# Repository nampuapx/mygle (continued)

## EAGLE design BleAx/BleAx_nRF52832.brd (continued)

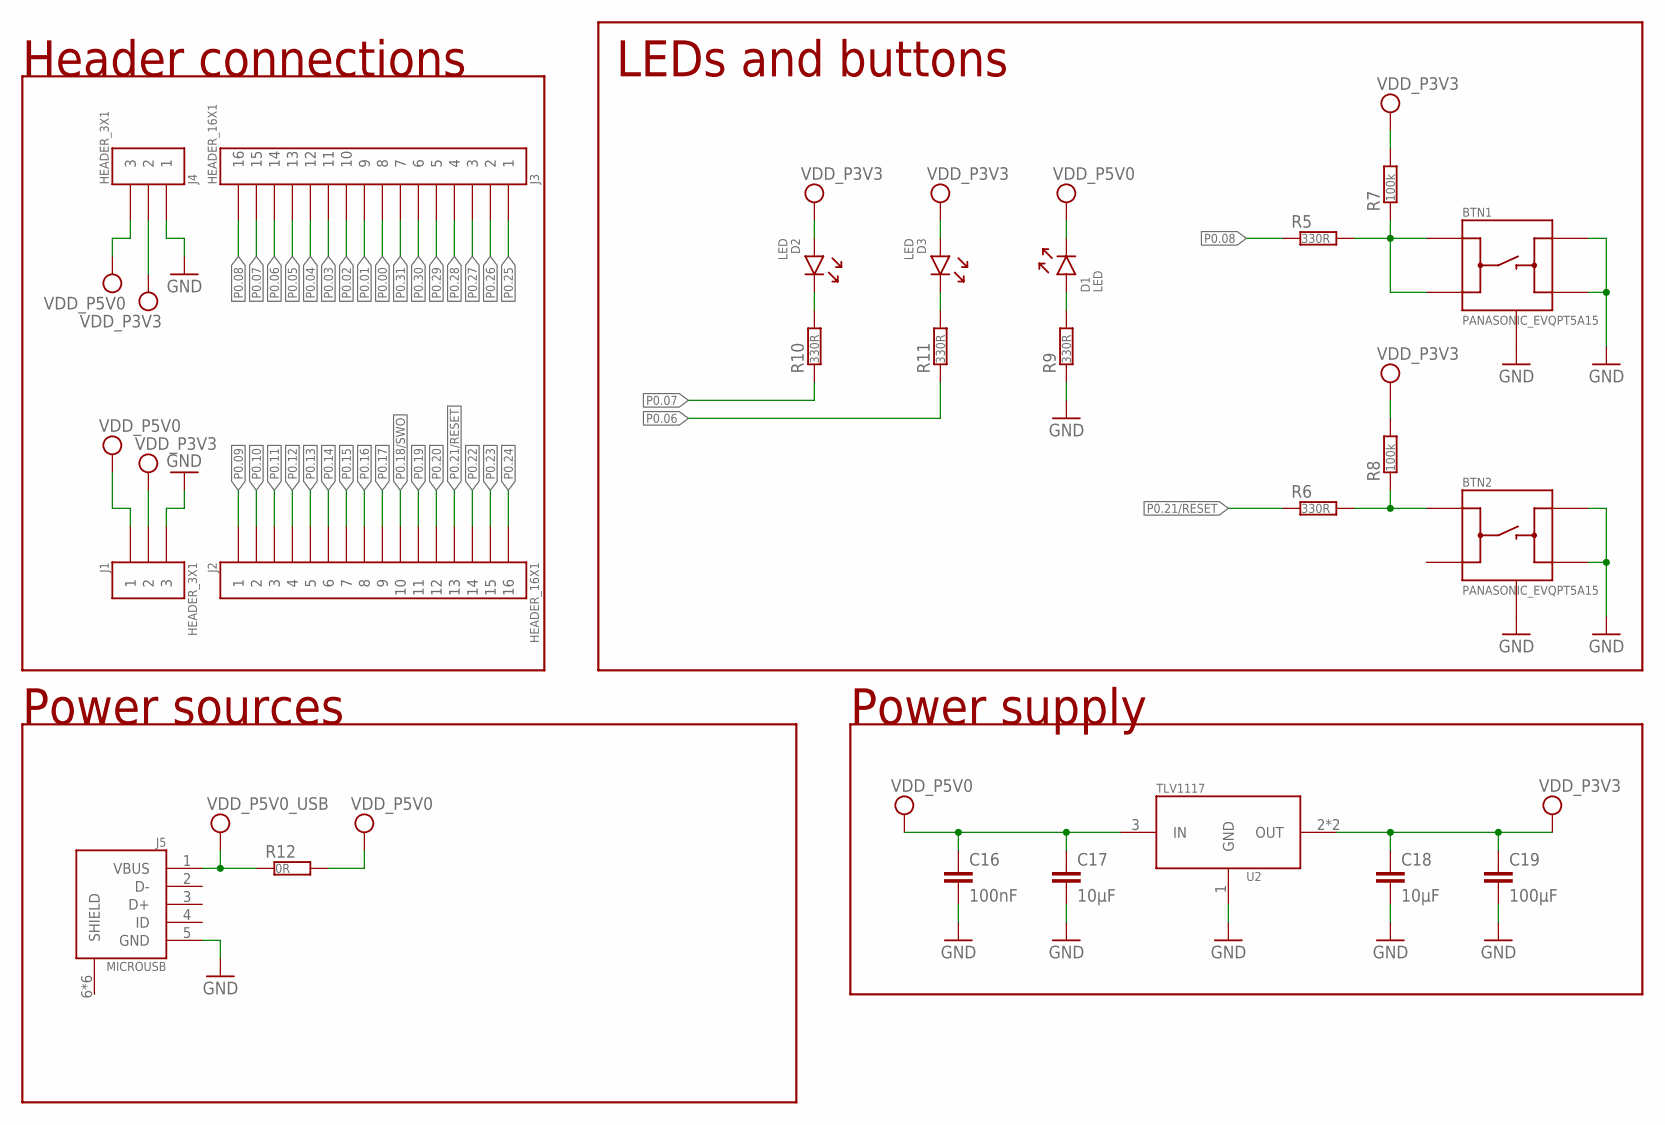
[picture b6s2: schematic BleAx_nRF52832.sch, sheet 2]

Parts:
BTN1, BTN2: PANASONIC_EVQPT5A15
C16: 100nF; RESC0402_N
C17, C18: 10µF; RESC0603_N
C19: 100µF; RESC0805_N
D1, D2, D3: LED; DIOC0603_N
J1, J4: HEADER_3X1; HDRV3W64P254_1X3_762X254X900B_NO_SILK
J2, J3: HEADER_16X1; HDRV16W64P254_1X16_4064X254X900B_NO_SILK
J5: MICROUSB; USB-MICRO-B-RA-SMD-PIP
R5, R6, R9, R10, R11: 330R; RESC0402_N
R7, R8: 100k; RESC0402_N
R12: 0R; RESC0402_N
U2: TLV1117; SOT220P700-4_N

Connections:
GND: BTN1.3 (B), BTN1.4 (B'), BTN1.5 (GND), BTN1.6 (GND), BTN2.3 (B), BTN2.4 (B'), BTN2.5 (GND), BTN2.6 (GND), C16.2, C17.2, C18.2, C19.2, J1.P$3 (3), J4.P$1 (1), J5.5 (GND), R9.1, U2.1 (GND); also elsewhere on the board
unnamed: BTN2.1 (A), R6.2, R8.1
unnamed: BTN1.1 (A), BTN1.2 (A'), R5.2, R7.1
unnamed: D2.1 (C), R10.2
unnamed: D3.1 (C), R11.2
P0.00: J3.P$8 (8)
P0.01: J3.P$9 (9)
P0.02: J3.P$10 (10); also elsewhere on the board
P0.03: J3.P$11 (11); also elsewhere on the board
P0.04: J3.P$12 (12); also elsewhere on the board
P0.05: J3.P$13 (13); also elsewhere on the board
P0.06: J3.P$14 (14), R11.1; also elsewhere on the board
P0.07: J3.P$15 (15), R10.1; also elsewhere on the board
P0.08: J3.P$16 (16), R5.1; also elsewhere on the board
P0.09: J2.P$1 (1); also elsewhere on the board
P0.10: J2.P$2 (2); also elsewhere on the board
P0.11: J2.P$3 (3); also elsewhere on the board
P0.12: J2.P$4 (4); also elsewhere on the board
P0.13: J2.P$5 (5); also elsewhere on the board
P0.14: J2.P$6 (6); also elsewhere on the board
P0.15: J2.P$7 (7); also elsewhere on the board
P0.16: J2.P$8 (8); also elsewhere on the board
P0.17: J2.P$9 (9); also elsewhere on the board
P0.18/SWO: J2.P$10 (10); also elsewhere on the board
P0.19: J2.P$11 (11); also elsewhere on the board
P0.20: J2.P$12 (12); also elsewhere on the board
P0.21/RESET: J2.P$13 (13), R6.1; also elsewhere on the board
P0.22: J2.P$14 (14); also elsewhere on the board
P0.23: J2.P$15 (15); also elsewhere on the board
P0.24: J2.P$16 (16); also elsewhere on the board
P0.25: J3.P$1 (1); also elsewhere on the board
P0.26: J3.P$2 (2); also elsewhere on the board
P0.27: J3.P$3 (3); also elsewhere on the board
P0.28: J3.P$4 (4); also elsewhere on the board
P0.29: J3.P$5 (5); also elsewhere on the board
P0.30: J3.P$6 (6); also elsewhere on the board
P0.31: J3.P$7 (7); also elsewhere on the board
VCC_P5V0_USB: J5.1 (VBUS), R12.1
VDD_LED: D1.2 (A), R9.2
VDD_P3V3: C18.1, C19.1, D2.2 (A), D3.2 (A), J1.P$2 (2), J4.P$2 (2), R7.2, R8.2, U2.2 (OUT), U2.4 (OUT); also elsewhere on the board
VDD_P5V0: C16.1, C17.1, D1.1 (C), J1.P$1 (1), J4.P$3 (3), R12.2, U2.3 (IN)

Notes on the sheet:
Power supply
Power sources
Header connections
LEDs and buttons

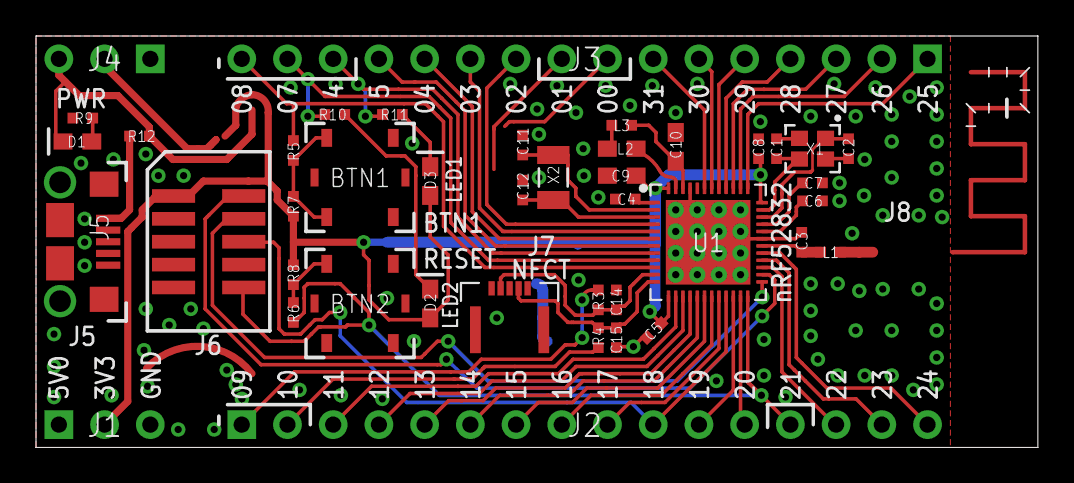
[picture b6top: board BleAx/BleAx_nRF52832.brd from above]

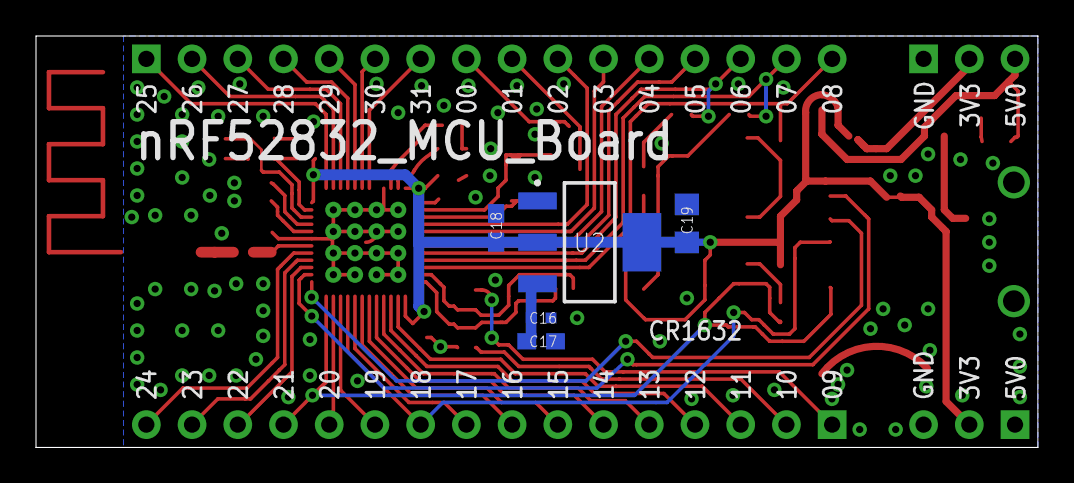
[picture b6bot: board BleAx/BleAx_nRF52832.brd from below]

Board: 2 copper layers, 55.7 x 22.9 mm, 48 parts (5 on the bottom side), 55 nets.

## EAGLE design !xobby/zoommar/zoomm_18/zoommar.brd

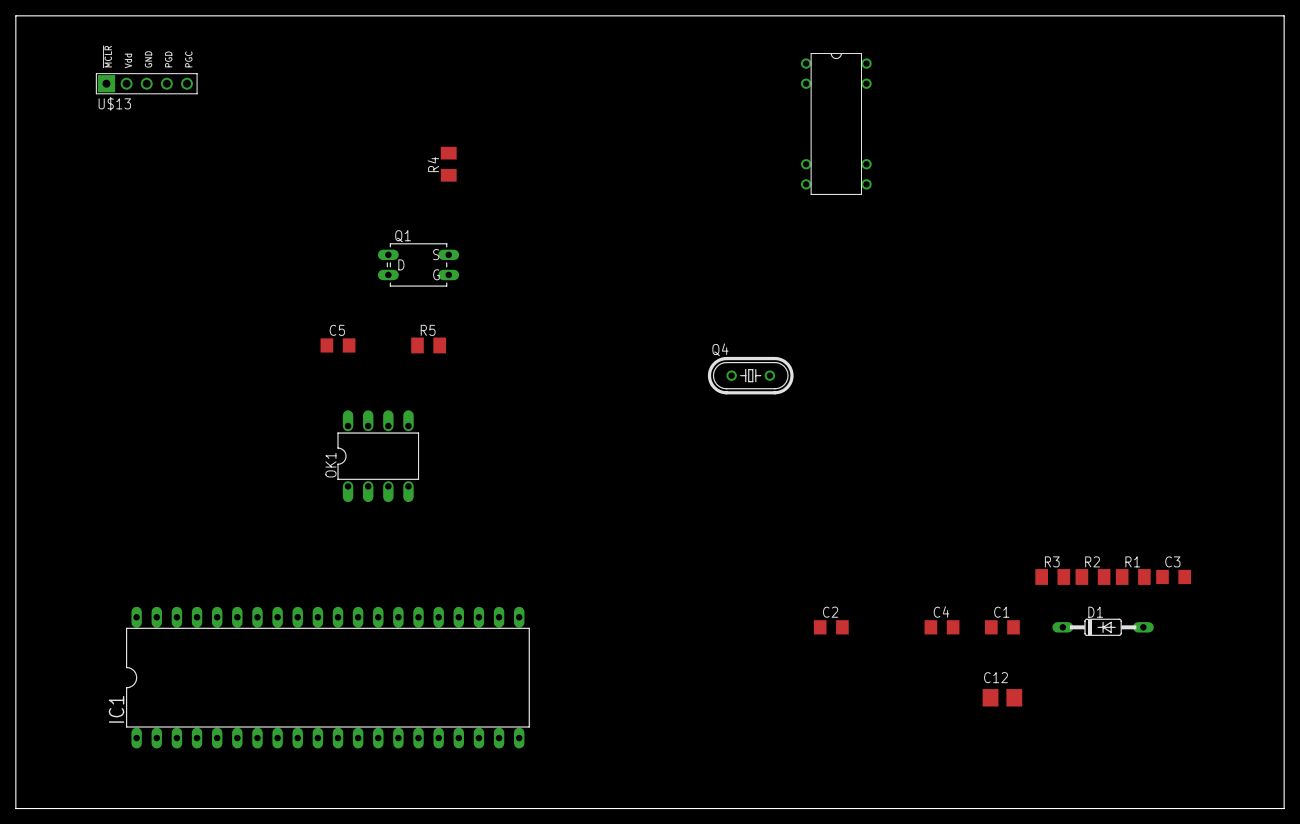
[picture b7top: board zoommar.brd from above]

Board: 2 copper layers, 160.0 x 100.0 mm, 18 parts (0 on the bottom side), 13 nets, no tracks yet.

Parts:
C1, C4, C5: 0.47uF; C1206
C2, C3: 15pF; C1206
C12: 10u; CT3528
D1: 1N4148DO35-10; DO35-10
IC1: PIC18F4550_40; DIL40
OK1: 6N138; DIL08
Q1: IRFD9120; C370-01
Q4: 20MHz; HC49/S
R1: 10k; M1206
R2: 3k3; M1206
R3: 220; M1206
R4: 10e; M1206
R5: 5k; M1206
U$1: TRR2A05D00; TRR_DIP
U$13: PIC-PROG-CON

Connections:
+5V: C1.2, C4.2, C12.-, IC1.11, IC1.32, OK1.8, R1.2, R2.2, R4.2, U$1.1
GND: C1.1, C2.2, C3.1, C4.1, C5.1, C12.+, IC1.12, IC1.31, OK1.5, Q1.D1, U$1.6, U$13.3
MCLR: IC1.1, R1.1, U$13.1
unnamed: IC1.40, U$13.4
unnamed: IC1.39, U$13.5
unnamed: Q1.S, R4.1, U$1.2
unnamed: D1.C, OK1.2, R3.1
unnamed: D1.A, OK1.3
unnamed: C5.2, Q1.G, R5.1
unnamed: R5.2, U$1.7
OSC@1: C2.1, Q4.1
OSC@2: C3.2, Q4.2
RX: IC1.26, OK1.6, R2.1

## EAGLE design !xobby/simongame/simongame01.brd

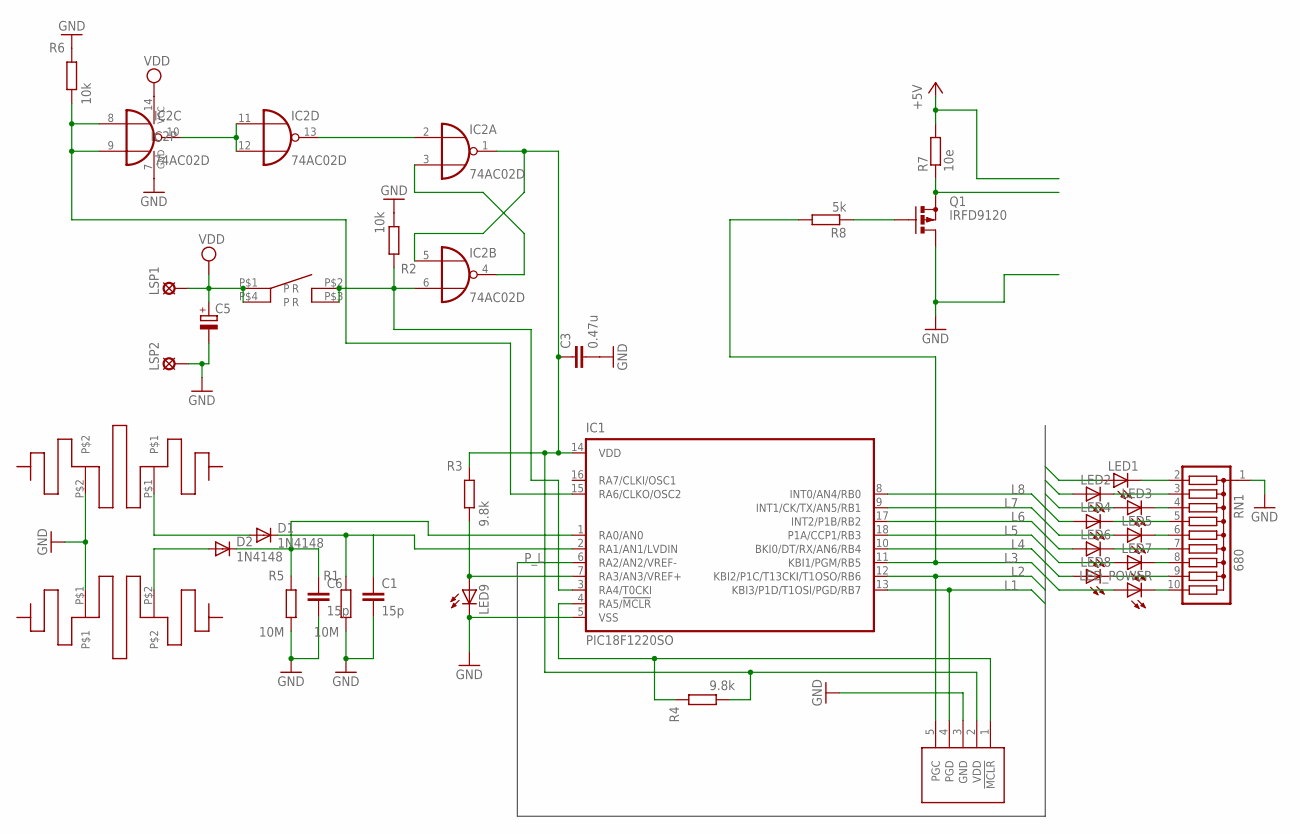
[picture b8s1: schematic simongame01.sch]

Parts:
C1, C6: 15p; C1206
C3: 0.47u; C1206
C5: CPOL-EUSMCA; SMC_A
D1, D2: 1N4148; DO35-10
IC1: PIC18F1220SO; SO-18W
IC2: 74AC02D; SO14
LED1, LED2, LED3, LED4, LED5, LED6, LED7, LED8: LED3MM
LED9: LED5MM
LED_POWER: LED3MM
LSP1, LSP2: SE14
Q1: IRFD9120; C370-01
R1, R5: 10M; M1206
R2, R6: 10k; M1206
R3, R4: 9.8k; M1206
R7: 10e; M1206
R8: 5k; M1206
RN1: 680; SIL10
U$1: TIKBUTTON01
U$2, U$3: ANTENNA; ANT!
U$4: PIC-PROG-CON

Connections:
+5V: R7.2
GND: C1.2, C3.2, C5.-, C6.2, IC1.5 (VSS), IC2.7 (GND), LED9.K (C), LSP2.MP, Q1.D1, R1.1, R2.1, R5.1, R6.2, RN1.1, U$2.P$1, U$3.P$2, U$4.3 (GND)
L1: IC1.13 (KBI3/P1D/T1OSI/PGD/RB7), LED1.A, U$4.4 (PGD)
L2: IC1.12 (KBI2/P1C/T13CKI/T1OSO/RB6), LED2.A, U$4.5 (PGC)
L3: IC1.11 (KBI1/PGM/RB5), LED3.A, R8.2
L4: IC1.10 (BKI0/DT/RX/AN6/RB4), LED4.A
L5: IC1.18 (P1A/CCP1/RB3), LED5.A
L6: IC1.17 (INT2/P1B/RB2), LED6.A
L7: IC1.9 (INT1/CK/TX/AN5/RB1), LED7.A
L8: IC1.8 (INT0/AN4/RB0), LED8.A
unnamed: C1.1, D1.C, IC1.2 (RA1/AN1/LVDIN), R1.2
unnamed: C6.1, D2.C, IC1.1 (RA0/AN0), R5.2
unnamed: LED1.K (C), RN1.2
unnamed: LED2.K (C), RN1.3
unnamed: LED3.K (C), RN1.4
unnamed: LED4.K (C), RN1.5
unnamed: LED5.K (C), RN1.6
unnamed: LED6.K (C), RN1.7
unnamed: LED7.K (C), RN1.8
unnamed: LED8.K (C), RN1.9
unnamed: LED_POWER.K (C), RN1.10
unnamed: C3.1, IC1.14 (VDD), IC2.1 (O), IC2.5 (I0), R3.2, R4.1, U$4.2 (VDD)
unnamed: IC2.3 (I1), IC2.4 (O)
unnamed: D1.A, U$3.P$1
unnamed: IC2.2 (I0), IC2.13 (O)
unnamed: IC1.3 (RA4/T0CKI), IC2.6 (I1), R2.2, U$1.P$2 (R), U$1.P$3 (R)
unnamed: D2.A, U$2.P$2
unnamed: IC1.7 (RA3/AN3/VREF+), LED9.A, R3.1
unnamed: IC2.10 (O), IC2.11 (I0), IC2.12 (I1)
unnamed: IC1.15 (RA6/CLKO/OSC2), IC2.8 (I0), IC2.9 (I1), R6.1
unnamed: IC1.4 (RA5/!MCLR), R4.2, U$4.1 (!MCLR)
unnamed: Q1.S, R7.1
unnamed: Q1.G, R8.1
P_L: IC1.6 (RA2/AN2/VREF-), LED_POWER.A
VDD: C5.+, IC2.14 (VCC), LSP1.MP, U$1.P$1, U$1.P$4

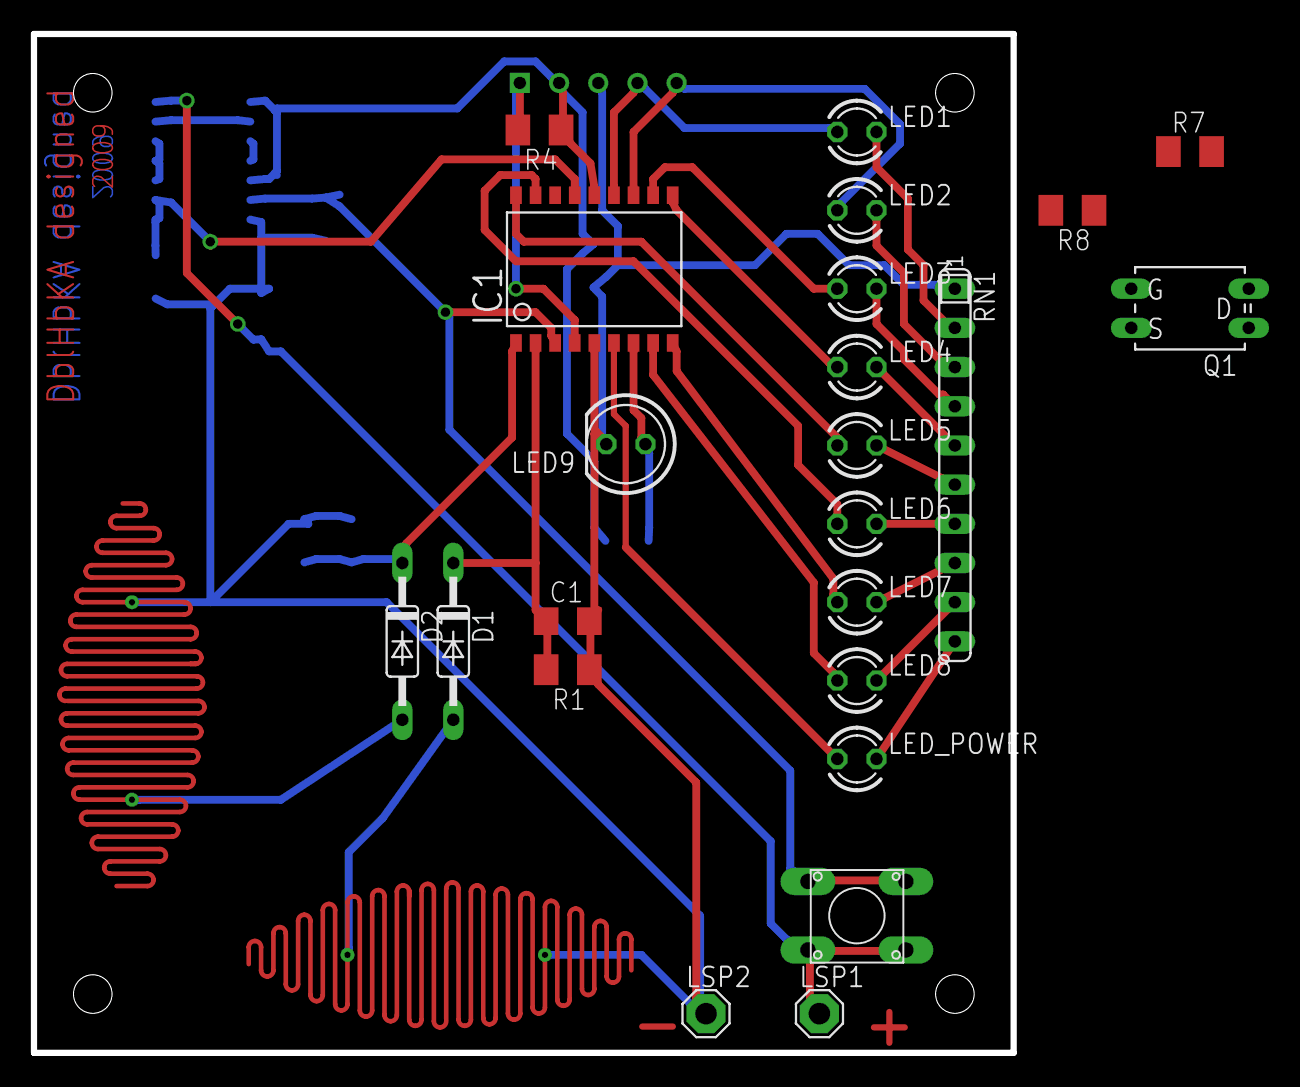
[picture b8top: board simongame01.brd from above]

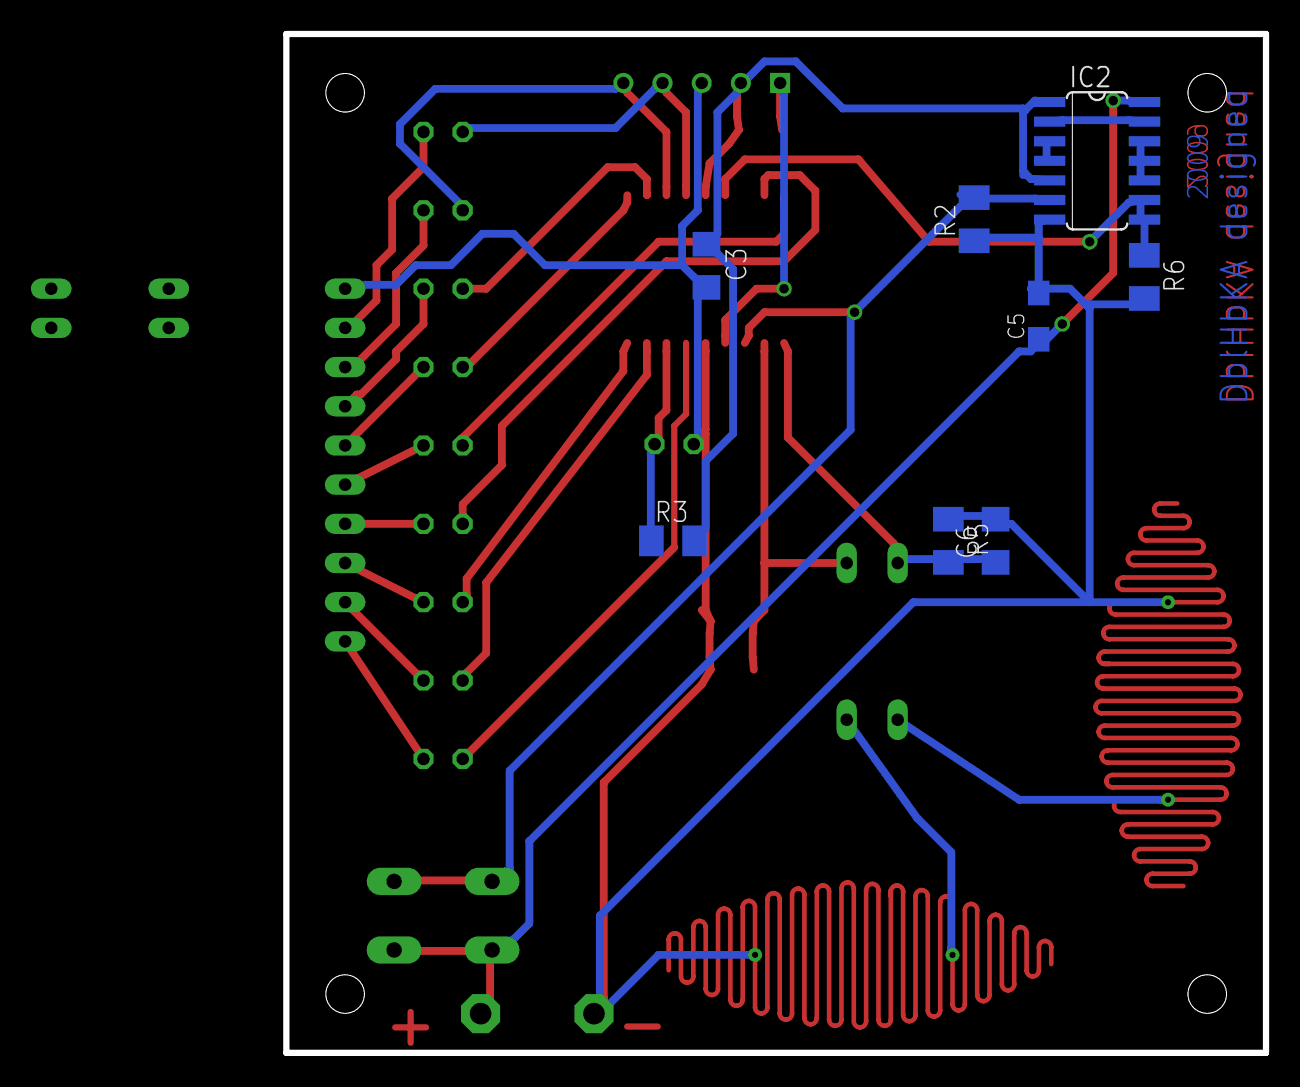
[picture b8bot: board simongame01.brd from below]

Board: 2 copper layers, 63.5 x 66.0 mm, 34 parts (8 on the bottom side), 34 nets.

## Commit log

2017-06-22 firstadd
2017-06-23 home gnome
2017-07-04 evolving
2017-07-04 nrf start
2017-07-05 rename
2017-07-05 cleaning
2017-07-05 lisaddeding
2017-07-05 conn prog
2017-07-05 power ldo
2017-07-05 batt source
2017-07-05 evolve
2017-07-05 sst26
2017-07-05 evolving pads added
2017-07-05 last today
2017-07-06 size decrise
2017-07-06 evolv
2017-07-06 ext lib add
2017-07-06 lib adding
2017-07-06 размеры уменьшил
2017-07-11 button del
2017-07-11 willl be think this is start point
2017-07-11 evolve_ button move down
2017-07-11 halfway?
2017-07-11 half half evolve
2017-07-11 75-80
2017-07-11 usb_change
2017-07-11 pred_auto
2017-07-11 pred_auto2
2017-07-13 pravki and gerbers
2017-07-18 11111111111
2017-07-20 sparkfun submodule add
2017-07-20 resistor value changed
2017-10-05 usb connector drew on stm32f103 board
2017-10-05 something added?
2017-10-05 led named
2017-10-12 wago add
2017-10-12 voron3_power add
2017-10-12 rase melon board started/add
2017-10-12 voron_pow evolve01
2017-10-17 first complete version
2017-10-18 voron3 evolve last version is voron3_power/v3pow_2_4v7
2017-10-25 voron3 evolve
2017-10-25 ra_se evolve
2017-11-01 oled and other
2017-11-15 voron pow evolve
2017-11-15 oled lib adding
2017-11-16 capacitor chan, and all done
2019-04-10 ra_se refactoring
2019-04-30 siga
2019-06-13 onion_led_add
